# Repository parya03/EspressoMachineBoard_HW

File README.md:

Espresso Machine Board Project
Make a new controller for my Chefman CraftBrew

### Rev 1 issues:
- Hole spacing for the HV board is off. Oh well.
- Terminal blocks for power input are not sized for 14 gauge wire, which is required for 15 amps. The holes for the terminal blocks aren't big enough to directly solder 14 gauge wire either.
- SOT-23 NMOS's have the wrong pinout (KiCad issue) and had to be soldered sideways

For Rev 2, might just remove HV side entirely and go with solid state relays instead.

TODO Documentation

Power converter KiCad symbol and footprint from:
https://github.com/yaserharba/WX-DC12003_Kicad

Reverse Engineering notes for now:

Single shot brew temp: ~180 F
Steam temp: ~205 F at valve, ~230F at boiler
NTC 100k(?) Thermistor
- ~114kOhm at ~22.5C
CMS79FT738 MCU
13 x 6 cm board
3/16” OD, 1/8”(?) ID tubing

Why is OPV before boiler? Where to put actual pressure sensor?

Label says 1350W power consumption, 120VAC 60Hz

Board mounting screw:
30-23.5‎ = 6.5 from edge of hole to edge of hole
Right side hole positioned at 3.5cm from top, 2.5mm from right side of board (to middle of hole)

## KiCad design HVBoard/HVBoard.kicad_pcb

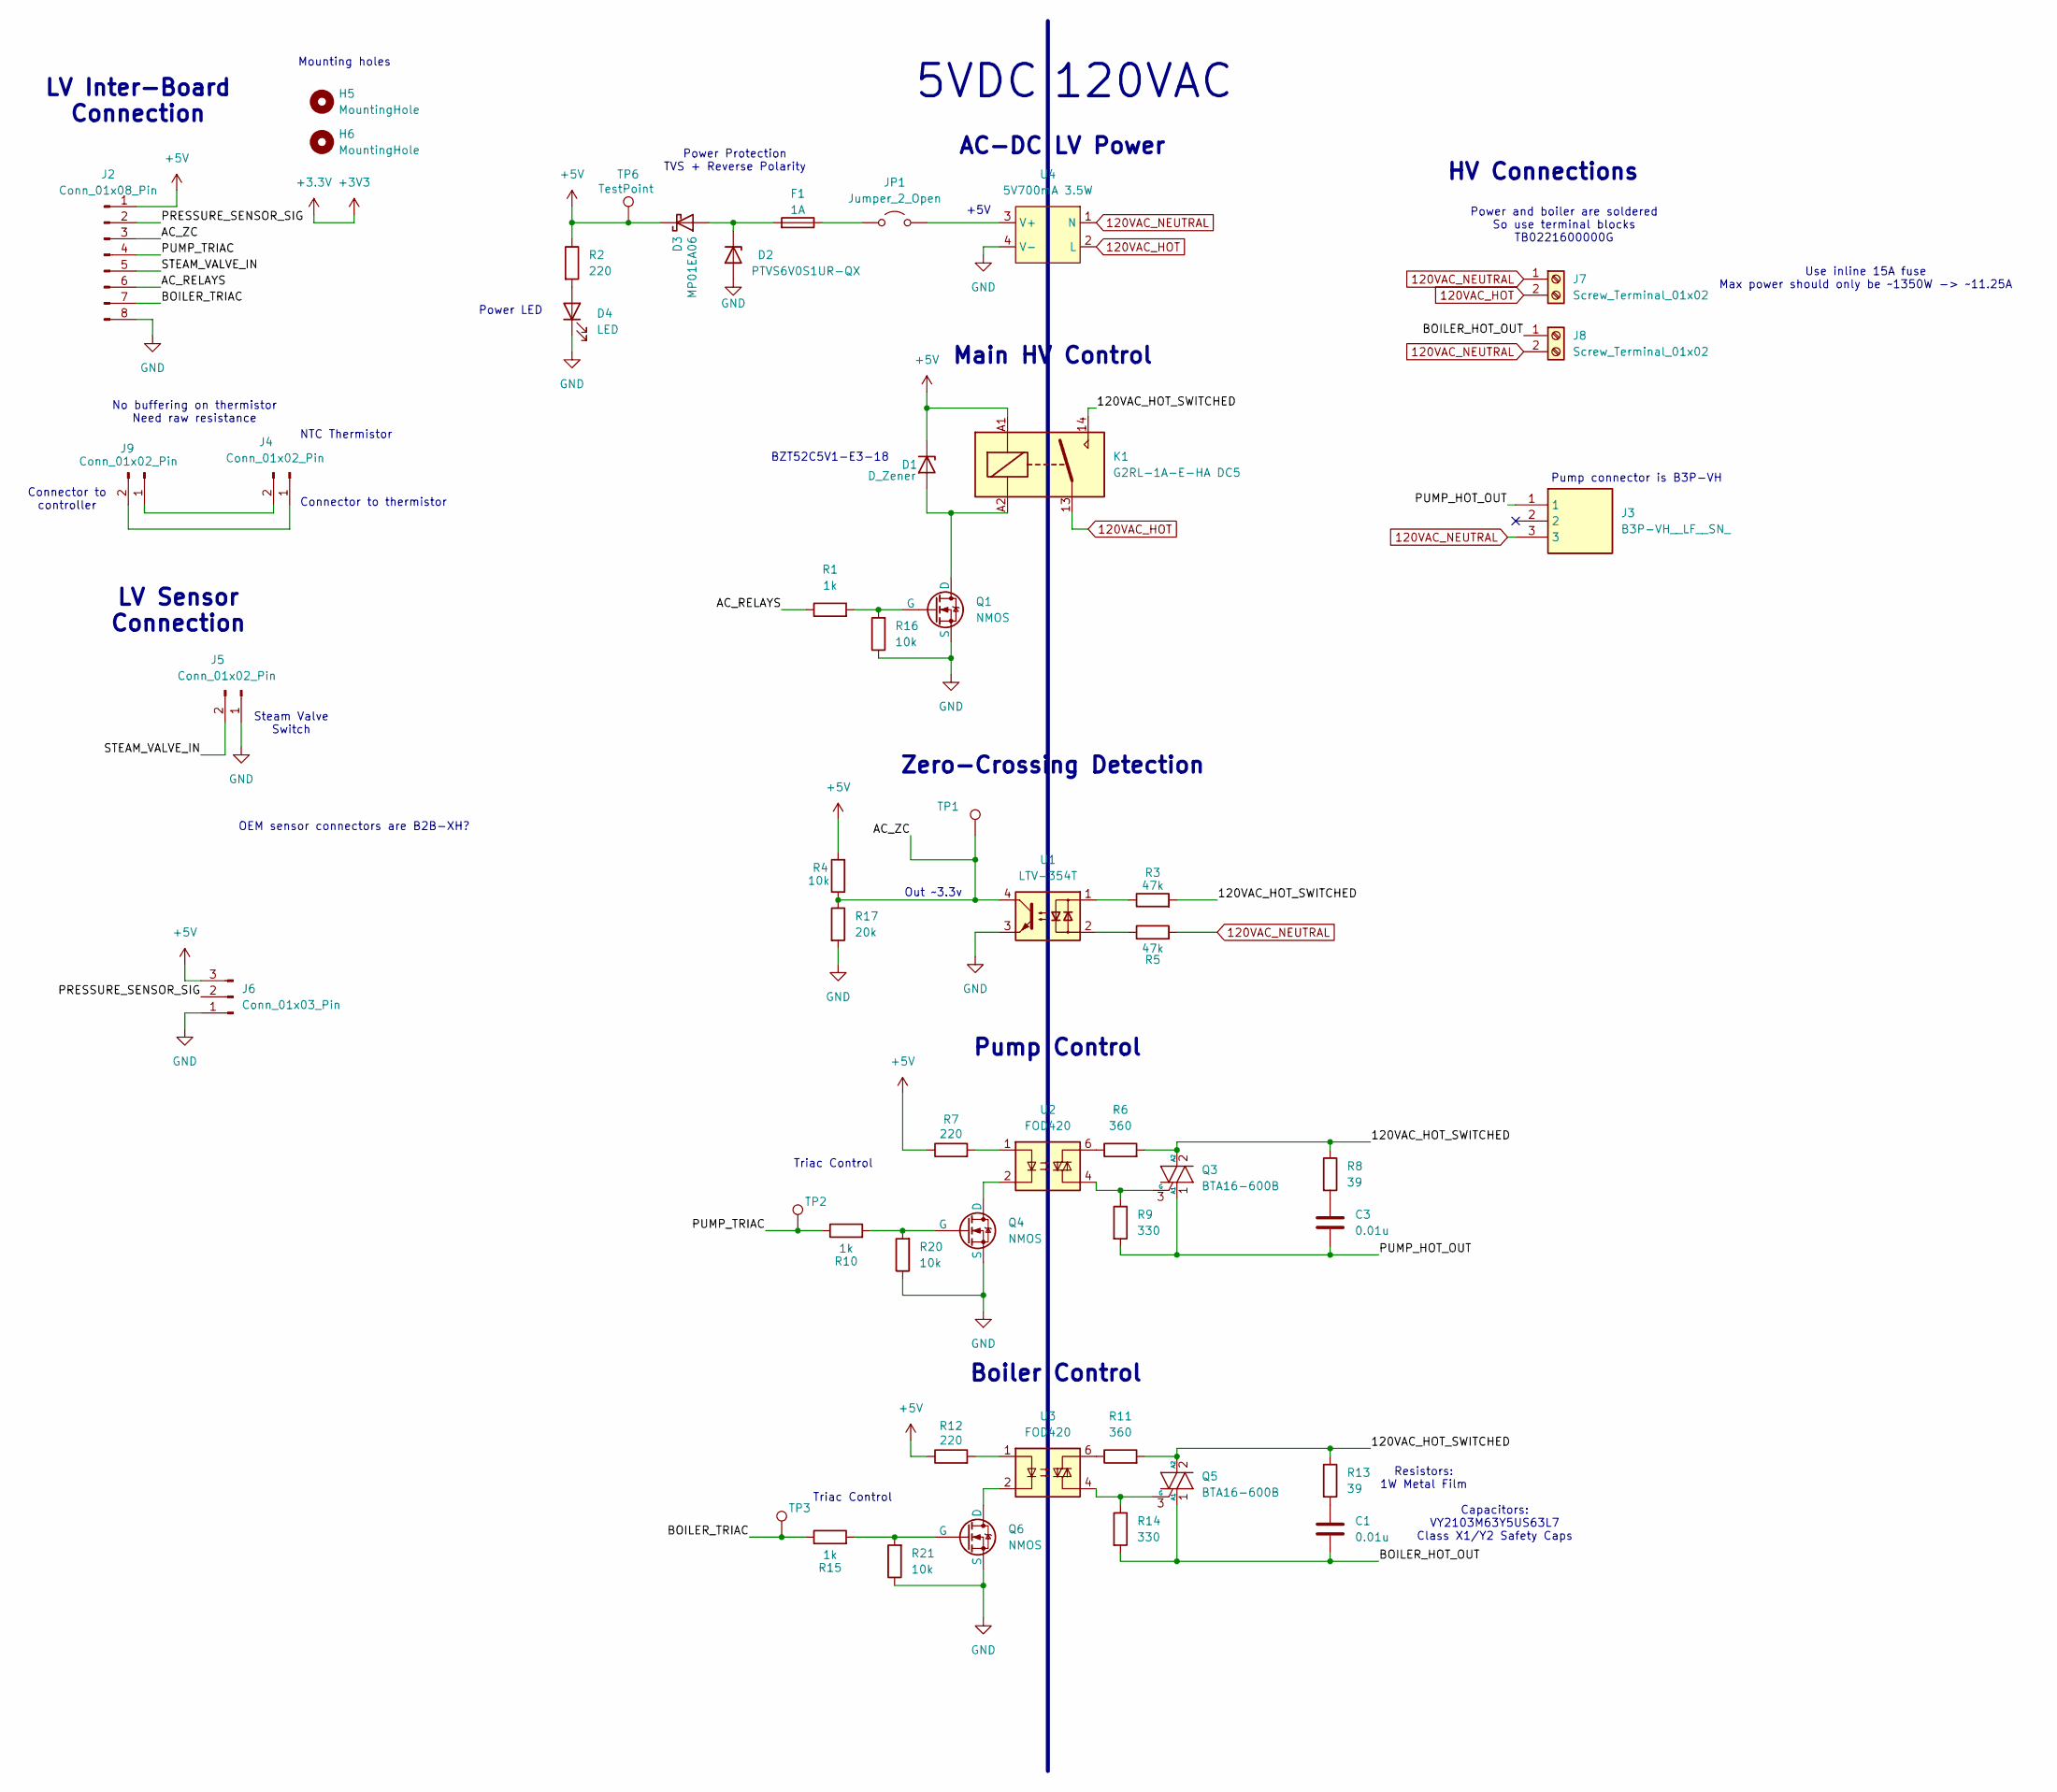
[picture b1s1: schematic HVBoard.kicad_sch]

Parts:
C1, C3: 0.01u; C_Disc_D11.0mm_W5.0mm_P7.50mm
D1: D_Zener; D_SOD-123
D2: PTVS6V0S1UR-QX; Nexperia_CFP3_SOD-123W
D3: MP01EA06; D_SOD-123
D4: LED; LED_0603_1608Metric; Mouser # 755-SMLD12EN1WT86
F1: 1A; Fuse_0603_1608Metric_Pad1.05x0.95mm_HandSolder
H5, H6: MountingHole; MountingHole_3.2mm_M3
J2: Conn_01x08_Pin; JST_PH_B8B-PH-K_1x08_P2.00mm_Vertical
J3: B3P-VH__LF__SN_; HDRV3W114P0X396_1X3_1182X850X1090P; Manufacturer_Part_Number B3P-VH (LF)(SN)
J4, J5, J9: Conn_01x02_Pin; JST_XH_B2B-XH-AM_1x02_P2.50mm_Vertical
J6: Conn_01x03_Pin; JST_XH_B3B-XH-AM_1x03_P2.50mm_Vertical
J7, J8: Screw_Terminal_01x02; TerminalBlock_bornier-2_P5.08mm
JP1: Jumper_2_Open; SolderJumper-2_P1.3mm_Open_Pad1.0x1.5mm
K1: G2RL-1A-E-HA DC5; Relay_SPST_Omron_G2RL-1A-E
Q1, Q4, Q6: NMOS; SOT-23
Q3, Q5: BTA16-600B; TO-220-3_Vertical
R1, R10, R15: 1k; R_0603_1608Metric_Pad0.98x0.95mm_HandSolder
R2: 220; R_0603_1608Metric; Mouser # 71-CRCW0603-665-E3
R3, R5: 47k; R_1206_3216Metric_Pad1.30x1.75mm_HandSolder
R4, R16, R20, R21: 10k; R_0603_1608Metric_Pad0.98x0.95mm_HandSolder
R6, R11: 360; R_1206_3216Metric_Pad1.30x1.75mm_HandSolder
R7, R12: 220; R_0603_1608Metric_Pad0.98x0.95mm_HandSolder
R8, R13: 39; R_Axial_DIN0207_L6.3mm_D2.5mm_P10.16mm_Horizontal
R9, R14: 330; R_1206_3216Metric_Pad1.30x1.75mm_HandSolder
R17: 20k; R_0603_1608Metric_Pad0.98x0.95mm_HandSolder
TP1, TP2, TP3, TP6: TestPoint; PinHeader_1x01_P2.54mm_Vertical
U1: LTV-354T; SO-4_4.4x3.6mm_P2.54mm
U2, U3: FOD420; DIP-6_W7.62mm
U4: 5V700mA 3.5W; WX-DC12003

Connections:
120VAC_HOT: J7.2, K1.13, U4.2 (L)
120VAC_NEUTRAL: J3.3, J7.1, J8.2, R5.2, U4.1 (N)
+5V: D1.1 (K), D3.1 (K), J2.1, J6.3, K1.A1, R2.1, R4.2, R7.1, R12.1, TP6.1
/120VAC_HOT_SWITCHED: K1.14, Q3.2 (A2), Q5.2 (A2), R3.2, R6.2, R8.1, R11.2, R13.1
/AC_RELAYS: J2.6, R1.1
/AC_ZC: J2.3, R4.1, R17.1, TP1.1, U1.4
/BOILER_HOT_OUT: C1.2, J8.1, Q5.1 (A1), R14.2
/BOILER_TRIAC: J2.7, R15.1, TP3.1
/PRESSURE_SENSOR_SIG: J2.2, J6.2
/PUMP_HOT_OUT: C3.2, J3.1, Q3.1 (A1), R9.2
/PUMP_TRIAC: J2.4, R10.1, TP2.1
/STEAM_VALVE_IN: J2.5, J5.2
GND: D2.2 (A), D4.1 (K), J2.8, J5.1, J6.1, Q1.3 (S), Q4.3 (S), Q6.3 (S), R16.1, R17.2, R20.1, R21.1, U1.3, U4.4 (V-)
unnamed: C1.1, R13.2
unnamed: C3.1, R8.2
unnamed: D1.2 (A), K1.A2, Q1.1 (D)
unnamed: D2.1 (K), D3.2 (A), F1.2
unnamed: D4.2 (A), R2.2
unnamed: J4.1, J9.2
unnamed: J4.2, J9.1
unnamed: JP1.1 (A), U4.3 (V+)
unnamed: F1.1, JP1.2 (B)
unnamed: Q1.2 (G), R1.2, R16.2
unnamed: Q3.3 (G), R9.1, U2.4
unnamed: Q4.1 (D), U2.2
unnamed: Q4.2 (G), R10.2, R20.2
unnamed: Q5.3 (G), R14.1, U3.4
unnamed: Q6.1 (D), U3.2
unnamed: Q6.2 (G), R15.2, R21.2
unnamed: R3.1, U1.1
unnamed: R5.1, U1.2
unnamed: R6.1, U2.6
unnamed: R7.2, U2.1
unnamed: R11.1, U3.6
unnamed: R12.2, U3.1

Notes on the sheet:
Connector to thermistor
Zero-Crossing Detection
Triac Control
Connector to controller
Mounting holes
Power and boiler are soldered So use terminal blocks TB0221600000G
+5V
Out ~3.3v
Power LED
Pump Control
OEM sensor connectors are B2B-XH?
Steam Valve Switch
5VDC
LV Inter-Board Connection
NTC Thermistor
Use inline 15A fuse Max power should only be ~1350W -> ~11.25A
BZT52C5V1-E3-18
AC-DC LV Power
Boiler Control
Pump connector is B3P-VH
No buffering on thermistor Need raw resistance
HV Connections
LV Sensor Connection
Main HV Control
Capacitors: VY2103M63Y5US63L7 Class X1/Y2 Safety Caps
Power Protection TVS + Reverse Polarity
Resistors: 1W Metal Film
120VAC

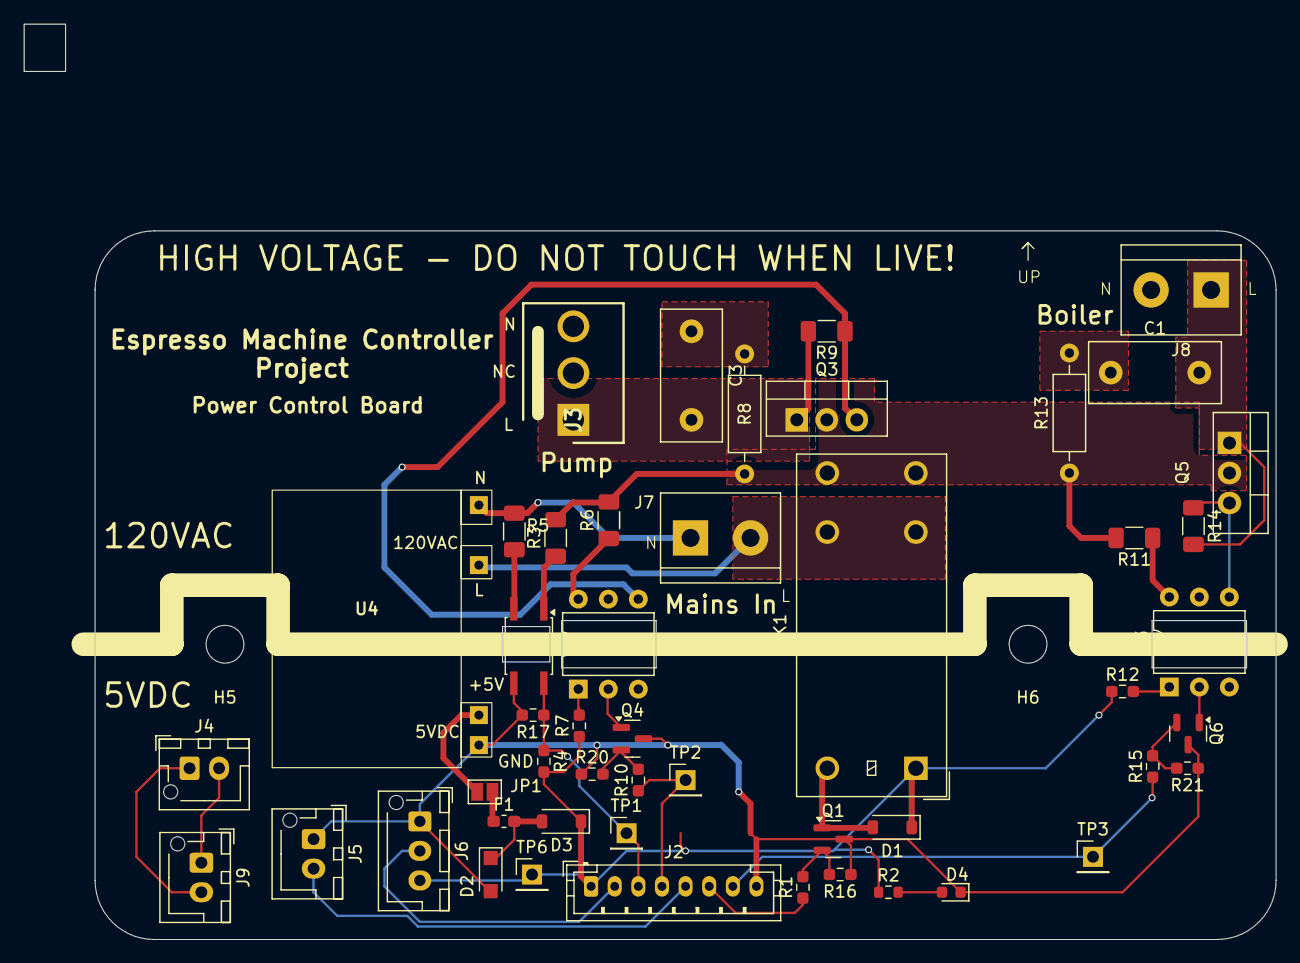
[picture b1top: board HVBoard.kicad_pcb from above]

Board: 2 copper layers, 106.0 x 77.5 mm, 51 parts (0 on the bottom side), 35 nets.

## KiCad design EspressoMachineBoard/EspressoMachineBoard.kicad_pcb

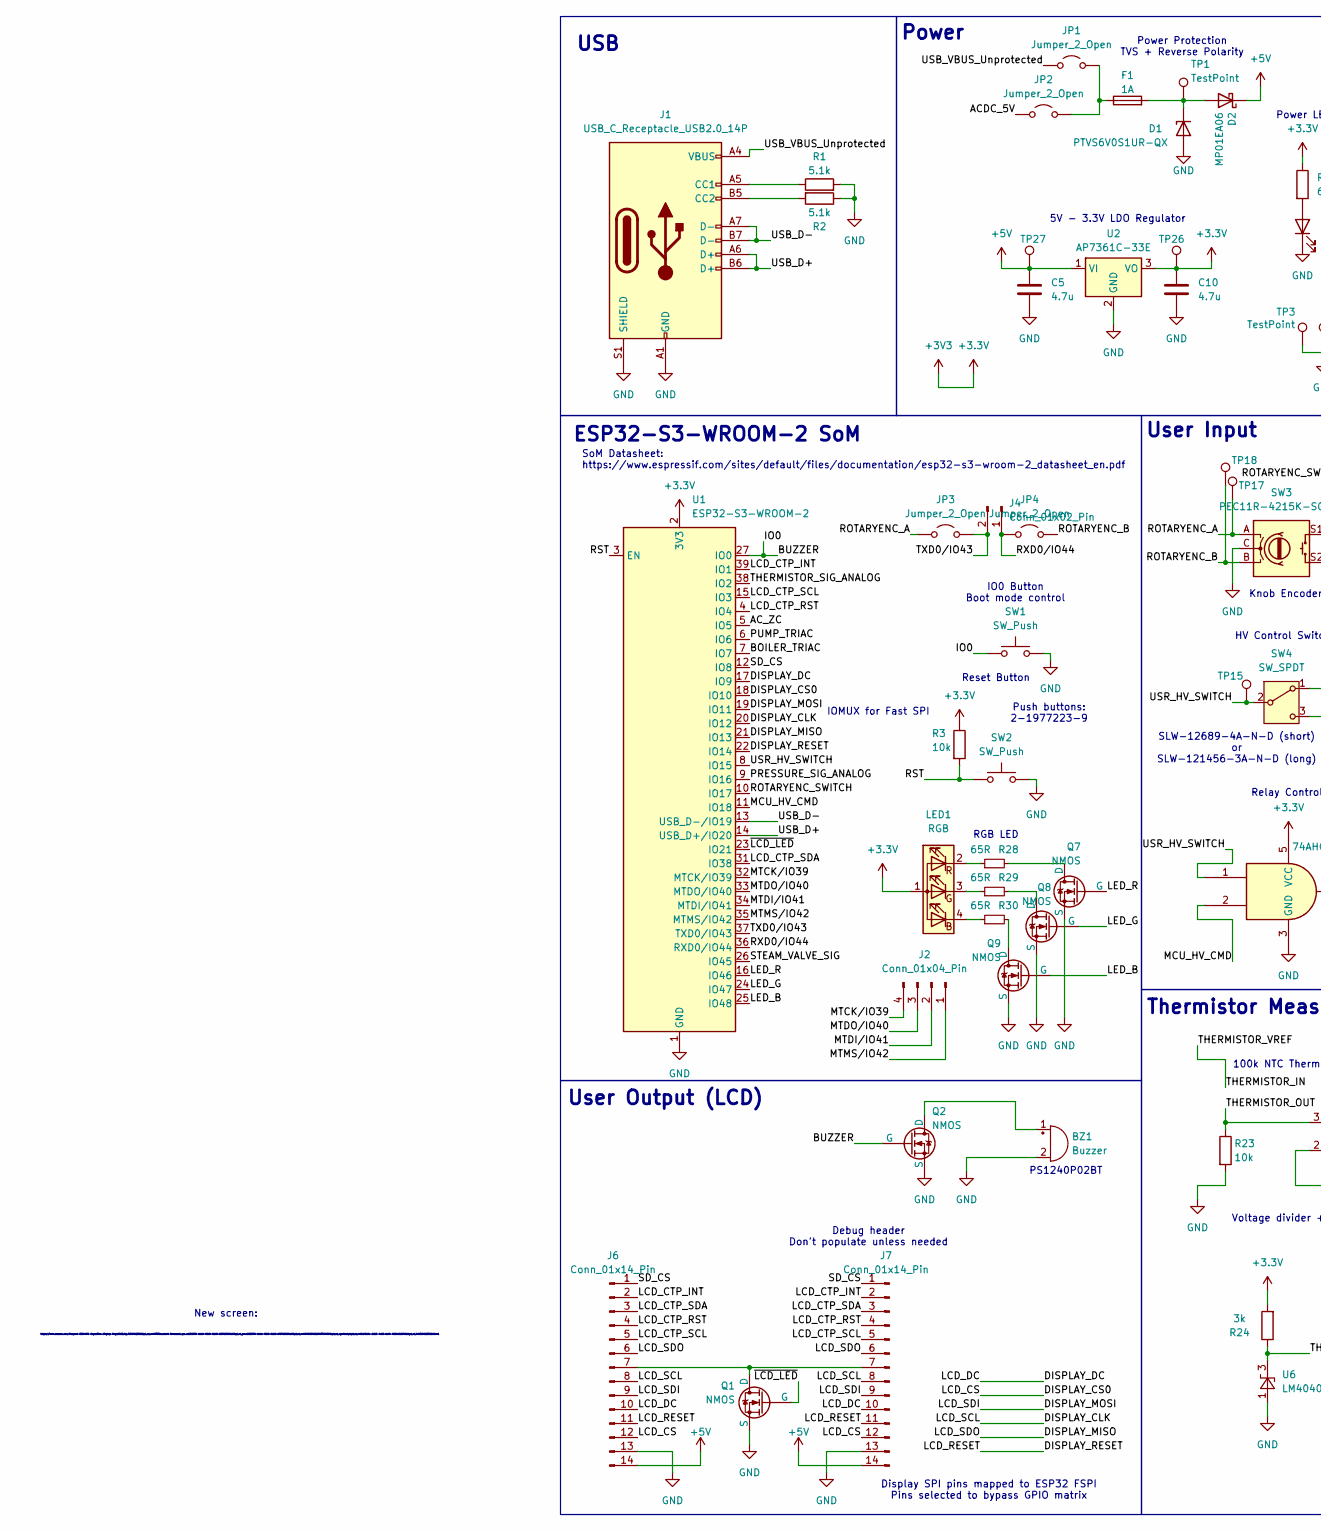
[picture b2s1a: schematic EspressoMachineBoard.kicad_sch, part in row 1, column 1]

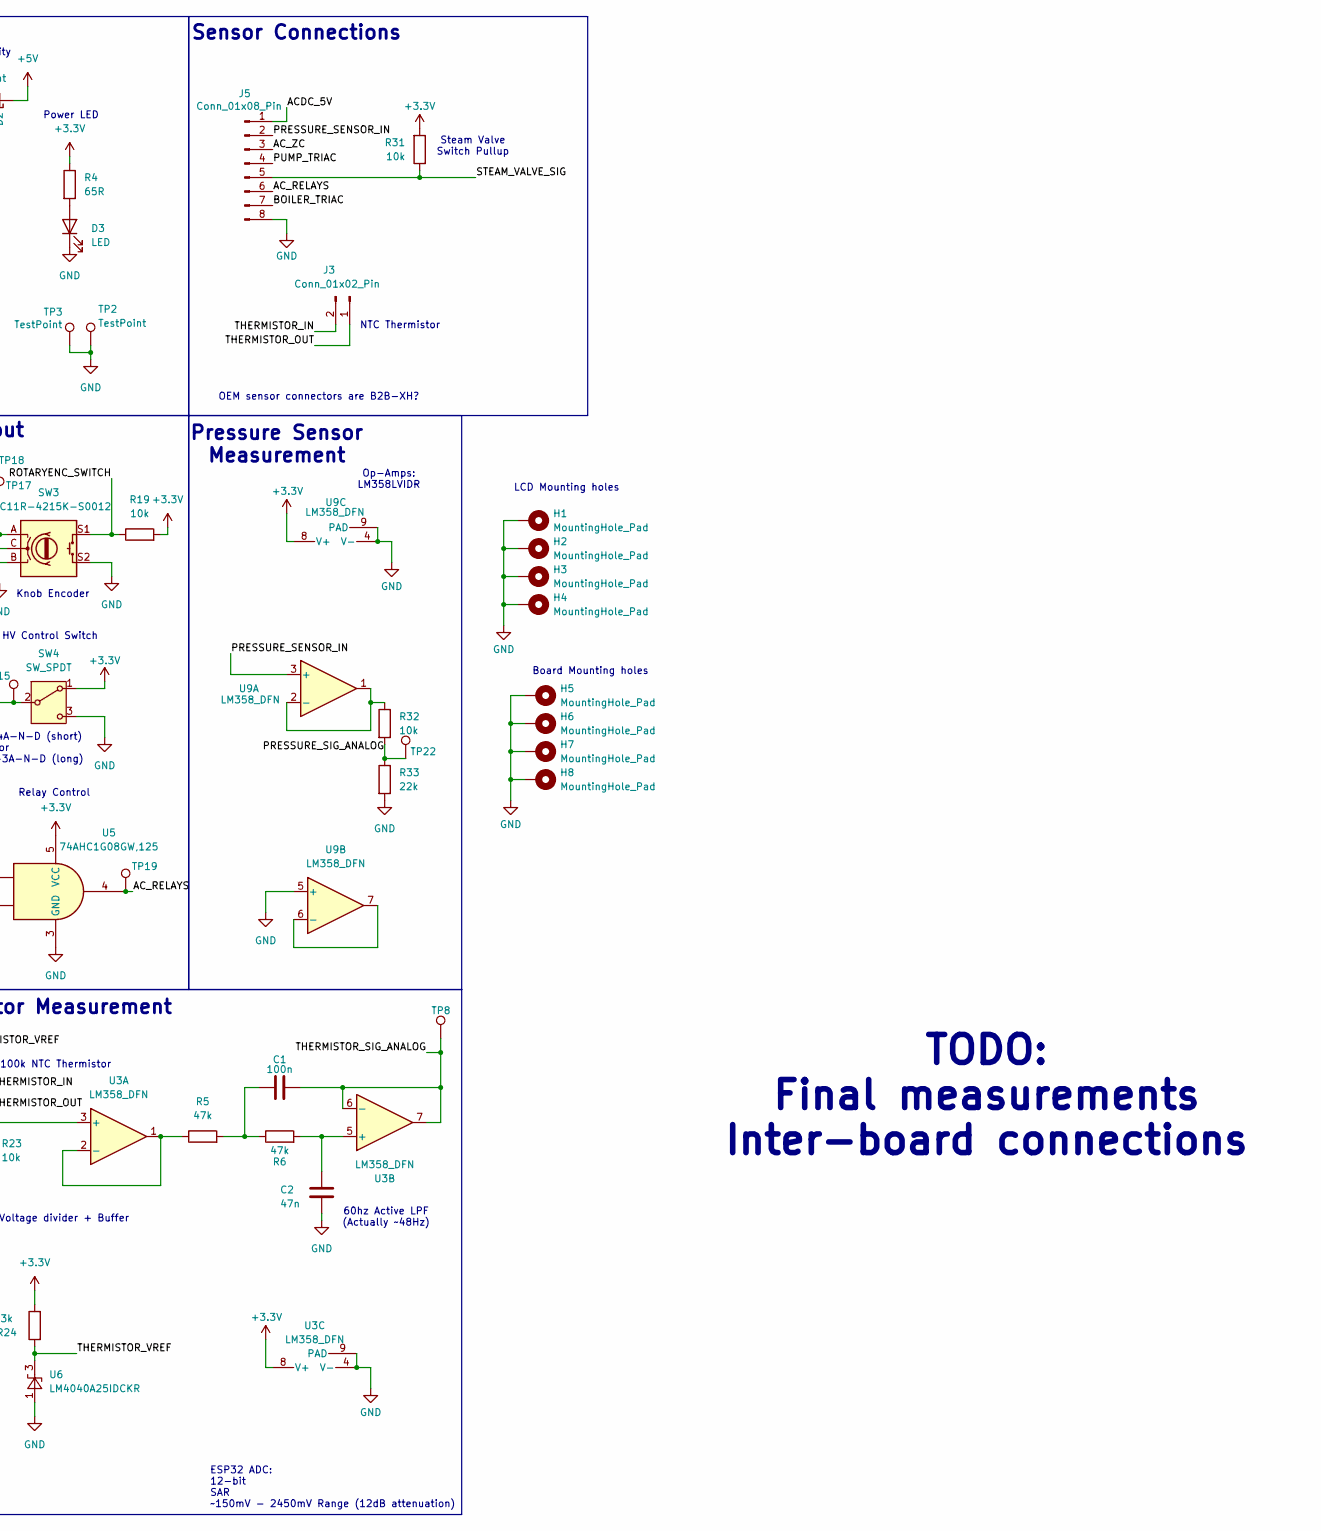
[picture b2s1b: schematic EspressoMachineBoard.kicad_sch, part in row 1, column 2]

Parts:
BZ1: Buzzer; Buzzer_TDK_PS1240P02BT_D12.2mm_H6.5mm
C1: 100n; C_0603_1608Metric_Pad1.08x0.95mm_HandSolder
C2: 47n; C_0603_1608Metric_Pad1.08x0.95mm_HandSolder
C5, C10: 4.7u; C_0603_1608Metric; Mouser # 81-GCJ188C70J475KE2D
D1: PTVS6V0S1UR-QX; Nexperia_CFP3_SOD-123W
D2: MP01EA06; D_SOD-123
D3: LED; LED_0603_1608Metric; Mouser # 755-SMLD12EN1WT86
F1: 1A; Fuse_0603_1608Metric_Pad1.05x0.95mm_HandSolder
H1, H2, H3, H4: MountingHole_Pad; MountingHole_3.2mm_M3_DIN965
H5, H6, H7, H8: MountingHole_Pad; MountingHole_3.2mm_M3_DIN965_Pad
J1: USB_C_Receptacle_USB2.0_14P; USB_C_Receptacle_GCT_USB4110
J2: Conn_01x04_Pin; PinSocket_1x04_P2.54mm_Vertical
J3: Conn_01x02_Pin; JST_XH_B2B-XH-AM_1x02_P2.50mm_Vertical
J4: Conn_01x02_Pin; PinSocket_1x02_P2.54mm_Vertical
J5: Conn_01x08_Pin; JST_PH_B8B-PH-K_1x08_P2.00mm_Vertical
J6, J7: Conn_01x14_Pin; PinSocket_1x14_P2.54mm_Vertical
JP1, JP2, JP3, JP4: Jumper_2_Open; SolderJumper-2_P1.3mm_Open_Pad1.0x1.5mm
LED1: RGB; LED_Cree-PLCC4_3.2x2.8mm_CCW; Mouser # 941-CLV1LFKBCJ1N1E1B
Q1, Q2, Q7, Q8, Q9: NMOS; SOT-23
R1, R2: 5.1k; R_0603_1608Metric_Pad0.98x0.95mm_HandSolder
R3, R19, R23, R31, R32: 10k; R_0603_1608Metric_Pad0.98x0.95mm_HandSolder
R4: 65R; R_0603_1608Metric; Mouser # 71-CRCW0603-665-E3
R5, R6: 47k; R_0603_1608Metric_Pad0.98x0.95mm_HandSolder
R24: 3k; R_0603_1608Metric_Pad0.98x0.95mm_HandSolder
R28, R29, R30: 65R; R_0603_1608Metric_Pad0.98x0.95mm_HandSolder
R33: 22k; R_0603_1608Metric_Pad0.98x0.95mm_HandSolder
SW1, SW2: SW_Push; SW_Push_1P1T_NO_6x6mm_H9.5mm
SW3: PEC11R-4215K-S0012; RotaryEncoder_Alps_EC11E-Switch_Vertical_H20mm
SW4: SW_SPDT; SW_Slide_SPDT_Straight_CK_OS102011MS2Q
TP1, TP2, TP3, TP8, TP15, TP17, TP18, TP19, TP22, TP26, TP27: TestPoint; PinHeader_1x01_P2.54mm_Vertical
U1: ESP32-S3-WROOM-2
U2: AP7361C-33E; SOT-223-3_TabPin2; Mouser # 621-AP7361C-33E-13
U3, U9: LM358_DFN; SOIC-8_3.9x4.9mm_P1.27mm
U5: 74AHC1G08GW,125; SOT-353_SC-70-5_Handsoldering
U6: LM4040A25IDCKR; SOT-353_SC-70-5

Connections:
+3.3V: C10.1, LED1.1 (A), R3.1, R4.1, R19.2, R24.2, R31.2, SW4.1 (A), TP26.1, U1.2 (3V3), U2.3 (VO), U3.8 (V+), U5.5 (VCC), U9.8 (V+)
+5V: C5.1, D2.1 (K), J6.14, J7.14, TP27.1, U2.1 (VI)
/ACDC_5V: J5.1, JP2.1 (A)
/AC_RELAYS: J5.6, TP19.1, U5.4
/AC_ZC: J5.3, U1.5 (IO5)
/BOILER_TRIAC: J5.7, U1.7 (IO7)
/BUZZER: Q2.2 (G), SW1.1, U1.27 (IO0)
/DISPLAY_CLK: J6.8, J7.8, U1.20 (IO12)
/DISPLAY_CS0: J6.12, J7.12, U1.18 (IO10)
/DISPLAY_DC: J6.10, J7.10, U1.17 (IO9)
/DISPLAY_MISO: J6.6, J7.6, U1.21 (IO13)
/DISPLAY_MOSI: J6.9, J7.9, U1.19 (IO11)
/DISPLAY_RESET: J6.11, J7.11, U1.22 (IO14)
/LCD_CTP_INT: J6.2, J7.2, U1.39 (IO1)
/LCD_CTP_RST: J6.4, J7.4, U1.4 (IO4)
/LCD_CTP_SCL: J6.5, J7.5, U1.15 (IO3)
/LCD_CTP_SDA: J6.3, J7.3, U1.31 (IO38)
/LED_B: Q9.2 (G), U1.25 (IO48)
/LED_G: Q8.2 (G), U1.24 (IO47)
/LED_R: Q7.2 (G), U1.16 (IO46)
/MCU_HV_CMD: U1.11 (IO18), U5.2
/MTCK/IO39: J2.4, U1.32 (MTCK/IO39)
/MTDI/IO41: J2.2, U1.34 (MTDI/IO41)
/MTDO/IO40: J2.3, U1.33 (MTDO/IO40)
/MTMS/IO42: J2.1, U1.35 (MTMS/IO42)
/PRESSURE_SENSOR_IN: J5.2, U9.3 (+)
/PRESSURE_SIG_ANALOG: R32.2, R33.1, TP22.1, U1.9 (IO16)
/PUMP_TRIAC: J5.4, U1.6 (IO6)
/ROTARYENC_A: JP3.1 (A), SW3.A, TP17.1
/ROTARYENC_B: JP4.2 (B), SW3.B, TP18.1
/ROTARYENC_SWITCH: R19.1, SW3.S1, U1.10 (IO17); also elsewhere on the board
/RST: R3.2, SW2.1, U1.3 (EN)
/RXD0/IO44: J4.1, JP4.1 (A), U1.36 (RXD0/IO44)
/SD_CS: J6.1, J7.1, U1.12 (IO8)
/STEAM_VALVE_SIG: J5.5, R31.1, U1.26 (IO45)
/THERMISTOR_IN: J3.2, R24.1, U6.3 (K)
/THERMISTOR_OUT: J3.1, R23.1, U3.3 (+)
/THERMISTOR_SIG_ANALOG: C1.1, TP8.1, U1.38 (IO2), U3.6 (-), U3.7
/TXD0/IO43: J4.2, JP3.2 (B), U1.37 (TXD0/IO43)
/USB_D+: J1.A6 (D+), J1.B6 (D+), U1.14 (USB_D+/IO20)
/USB_D-: J1.A7 (D-), J1.B7 (D-), U1.13 (USB_D-/IO19)
/USB_VBUS_Unprotected: J1.A4 (VBUS), J1.A9 (VBUS), J1.B4 (VBUS), J1.B9 (VBUS), JP1.1 (A)
/USR_HV_SWITCH: SW4.2 (B), TP15.1, U1.8 (IO15), U5.1
/~LCD_LED: Q1.2 (G), U1.23 (IO21)
GND: BZ1.2 (-), C2.2, C5.2, C10.2, D1.2 (A), D3.1 (K), H1.1, H2.1, H3.1, H4.1, H5.1, H6.1, H7.1, H8.1, J1.A1 (GND), J1.A12 (GND), J1.B1 (GND), J1.B12 (GND), J1.S1 (SHIELD), J5.8, J6.13, J7.13, Q1.3 (S), Q2.3 (S), Q7.3 (S), Q8.3 (S), Q9.3 (S), R1.2, R2.1, R23.2, R33.2, SW1.2, SW2.2, SW3.C, SW3.S2, SW4.3 (C), TP2.1, TP3.1, U1.1 (GND), U1.40 (GND), U1.41 (GND), U2.2 (GND), U3.4 (V-), U3.9 (PAD), U5.3 (GND), U6.1 (A), U9.4 (V-), U9.5 (+), U9.9 (PAD)
unnamed: BZ1.1 (+), Q2.1 (D)
unnamed: C1.2, R5.2, R6.1
unnamed: D1.1 (K), D2.2 (A), F1.2, TP1.1
unnamed: D3.2 (A), R4.2
unnamed: J1.A5 (CC1), R1.1
unnamed: J1.B5 (CC2), R2.2
unnamed: J6.7, J7.7, Q1.1 (D)
unnamed: F1.1, JP1.2 (B), JP2.2 (B)
unnamed: LED1.4 (BK), R30.1
unnamed: LED1.3 (GK), R29.1
unnamed: LED1.2 (RK), R28.1
unnamed: Q7.1 (D), R28.2
unnamed: Q8.1 (D), R29.2
unnamed: Q9.1 (D), R30.2
unnamed: R5.1, U3.1, U3.2 (-)
unnamed: C2.1, R6.2, U3.5 (+)
unnamed: R32.1, U9.1, U9.2 (-)
unnamed: U9.6 (-), U9.7

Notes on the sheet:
60hz Active LPF (Actually ~48Hz)
Thermistor Measurement
Debug header Don't populate unless needed
ESP32 ADC: 12-bit SAR ~150mV - 2450mV Range (12dB attenuation)
SLW-12689-4A-N-D (short) or SLW-121456-3A-N-D (long)
OEM sensor connectors are B2B-XH?
Steam Valve Switch Pullup
Push buttons: 2-1977223-9
Relay Control
100k NTC Thermistor
User Input
Board Mounting holes
New screen:
IOMUX for Fast SPI
Power LED
Power Protection TVS + Reverse Polarity
5V - 3.3V LDO Regulator
SoM Datasheet: https://www.espressif.com/sites/default/files/documentation/esp32-s3-wroom-2_datasheet_en.pdf
Pressure Sensor Measurement
TODO: Final measurements Inter-board connections
Reset Button
Voltage divider + Buffer
User Output (LCD)
USB
RGB LED
ESP32-S3-WROOM-2 SoM
LCD Mounting holes
Sensor Connections
HV Control Switch
Knob Encoder
PS1240P02BT
Power
https://www.amazon.com/Hosyond-320x480-Capacitive-Display-Mega2560/dp/B0CRGQN58D?pd_rd_w=MfTtT&content-id=amzn1.sym.cd152278-debd-42b9-91b9-6f271389fda7&pf_rd_p=cd152278-debd-42b9-91b9-6f271389fda7&pf_rd_r=4CVHM0RG5QGXJTRP6XDY&pd_rd_wg=Nnetp&pd_rd_r=2bbf2a5e-2d15-4c26-bcf4-4226e2b3f481&pd_rd_i=B0CR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
Display SPI pins mapped to ESP32 FSPI Pins selected to bypass GPIO matrix
Op-Amps: LM358LVIDR
IO0 Button Boot mode control
NTC Thermistor

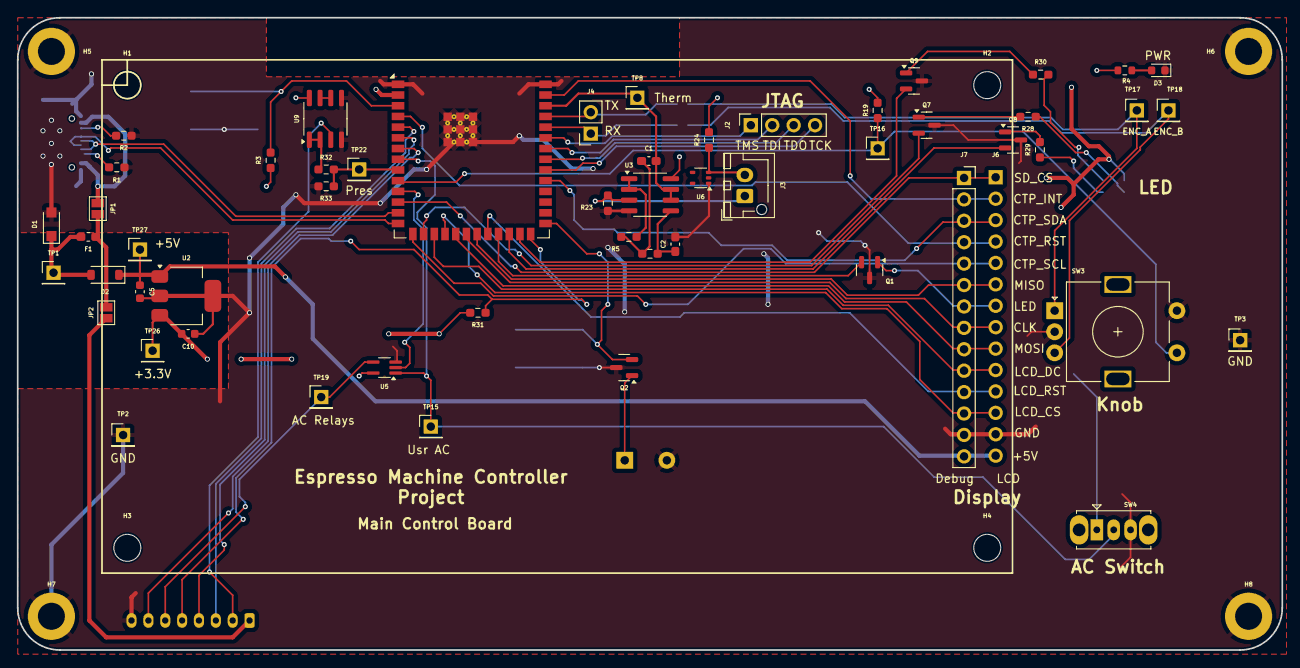
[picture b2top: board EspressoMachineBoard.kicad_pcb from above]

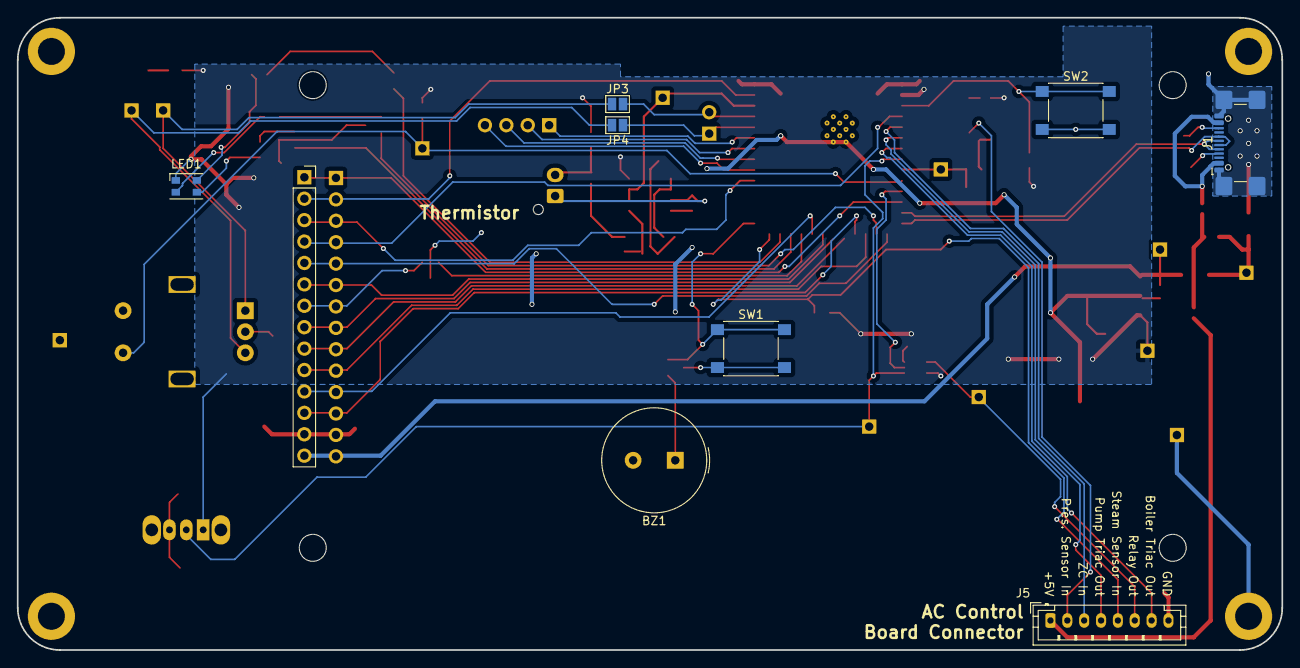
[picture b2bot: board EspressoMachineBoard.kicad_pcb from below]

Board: 2 copper layers, 150.0 x 75.0 mm, 71 parts (9 on the bottom side), 63 nets.

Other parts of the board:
TP16: TestPoint; PinHeader_1x01_P2.54mm_Vertical

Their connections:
/ROTARYENC_SWITCH: TP16.1; also elsewhere on the board

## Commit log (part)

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2024-12-19 Schematic initial commit
2024-12-20 Almost done with schematic
2024-12-20 Split into 2 board
2024-12-22 More work
2024-12-25 More HV work
2025-01-04 Reddit feedback integrated into HV board
2025-01-07 Boards finalized and ordered
2025-02-12 Added issues
2025-09-02 Updated Rev 1 to start new Rev
2025-11-11 Enclosure model started
